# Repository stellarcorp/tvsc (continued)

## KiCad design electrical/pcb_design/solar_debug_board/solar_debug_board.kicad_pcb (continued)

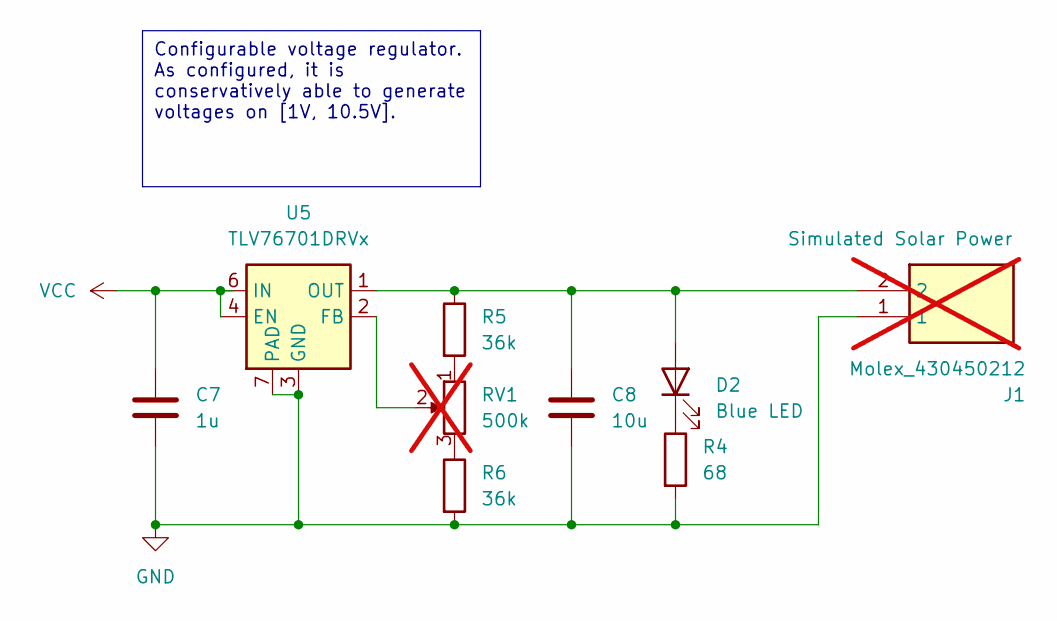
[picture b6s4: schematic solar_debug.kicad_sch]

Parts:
C7: 1u; C_0805_2012Metric; MPN C726584
C8: 10u; Nondescript_C_0603_1608Metric; MPN C344022
D2: Blue LED; LED_0603_1608Metric; MPN C72041
J1: Molex_430450212; Manufacturer Part Number 430450212; not fitted
R4: 68; R_0402_1005Metric; MPN C163455
R5, R6: 36k; R_0402_1005Metric; MPN C852742
RV1: 500k; Potentiometer_Bourns_3339H_Vertical; Tolerance 20%; Manufacturer Part Number 3339H-1-504LF; not fitted
U5: TLV76701DRVx; WSON-6-1EP_2x2mm_P0.65mm_EP1x1.6mm_ThermalVias; MPN C2863998

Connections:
GND: C7.2, C8.2, J1.1, R4.2, R6.2, U5.3 (GND), U5.5 (GND), U5.7 (PAD); also elsewhere on the board
unnamed: C8.1, D2.2 (A), J1.2, R5.1, U5.1 (OUT)
unnamed: D2.1 (K), R4.1
unnamed: R5.2, RV1.1
unnamed: R6.1, RV1.3
unnamed: RV1.2, U5.2 (FB)
VCC: C7.1, U5.4 (EN), U5.6 (IN); also elsewhere on the board

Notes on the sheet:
Configurable voltage regulator. As configured, it is conservatively able to generate voltages on [1V, 10.5V].

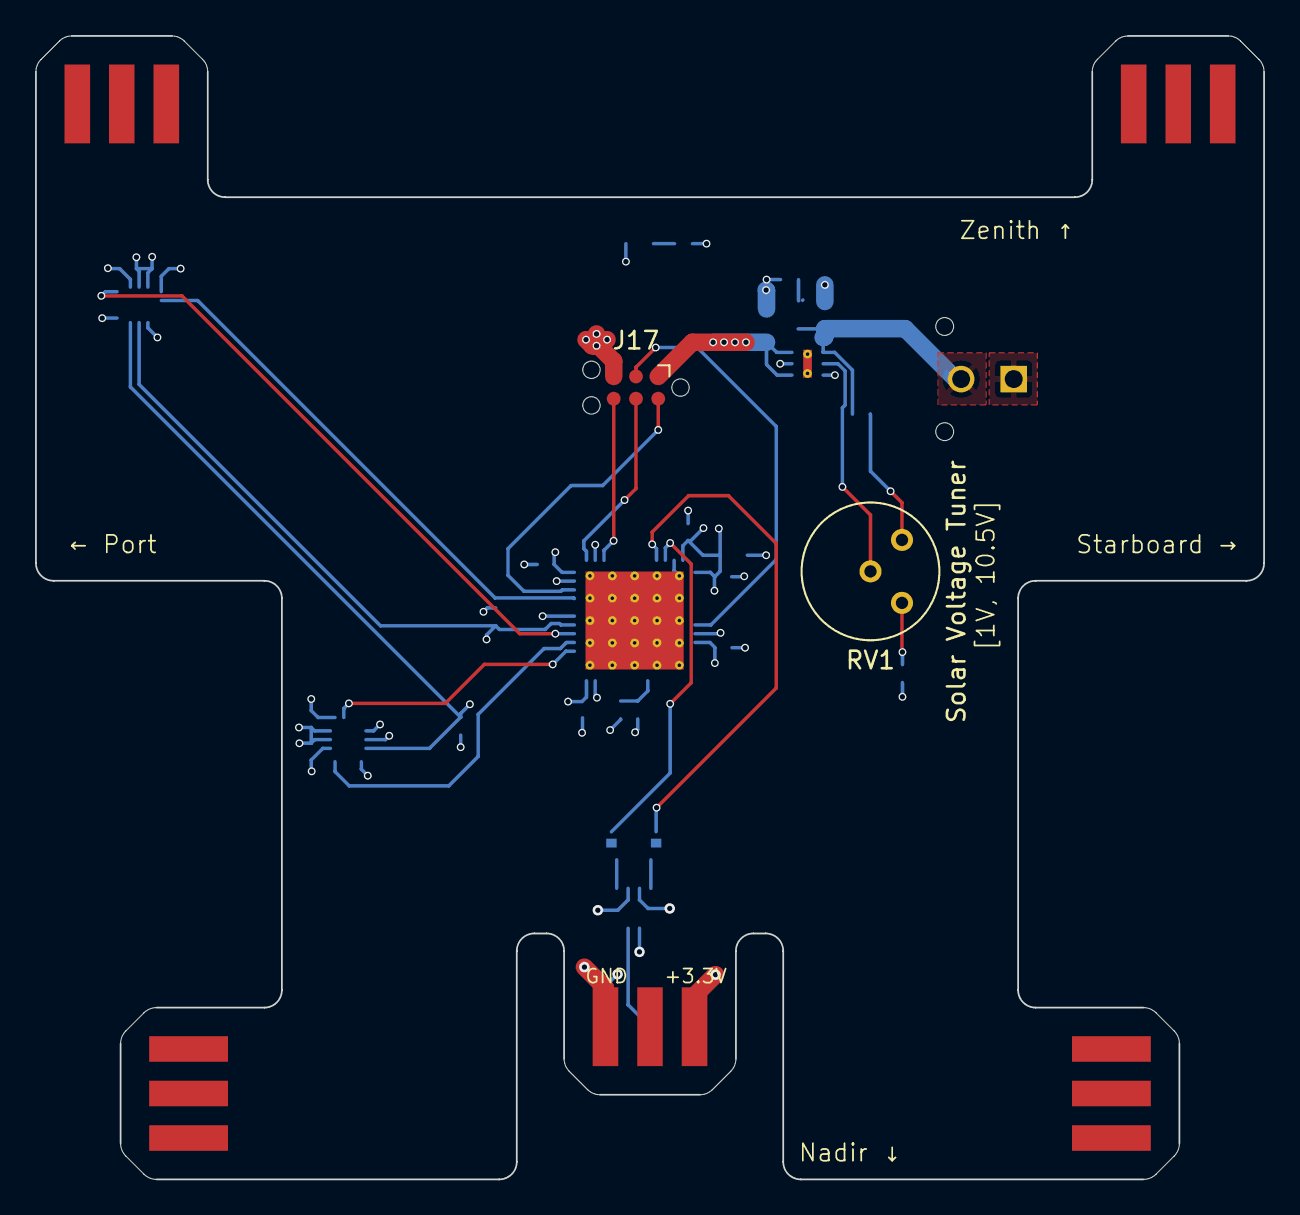
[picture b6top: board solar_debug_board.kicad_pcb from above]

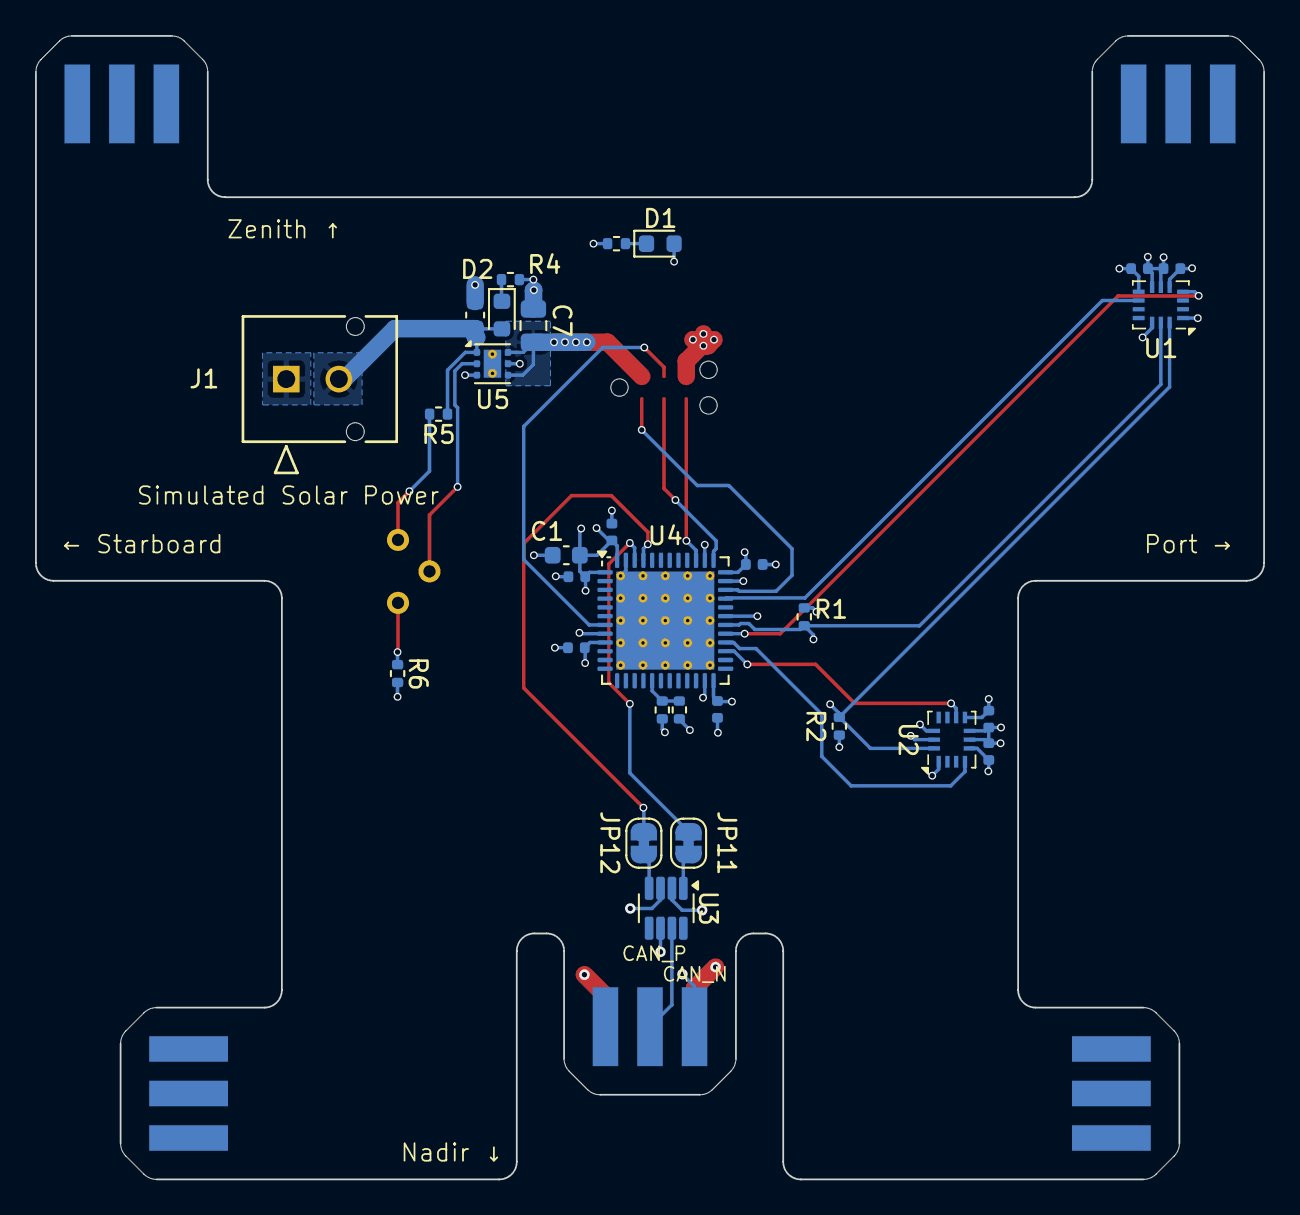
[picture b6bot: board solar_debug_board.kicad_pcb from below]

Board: 4 copper layers, 70.1 x 65.2 mm, 33 parts (30 on the bottom side), 27 nets.

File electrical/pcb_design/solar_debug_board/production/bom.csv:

Designator,Footprint,Quantity,Value,LCSC Part #
C1,0603,1,10u,C344022
"C10, C11, C12, C2, C3, C4, C5, C6, C9",Nondescript_C_0402_1005Metric,9,100n,C2649549
C7,0805,1,1u,C726584
C8,Nondescript_C_0603_1608Metric,1,10u,C344022
"D1, D2",0603,2,Blue LED,C72041
"JP11, JP12",SolderJumper-2_P1.3mm_Bridged_RoundedPad1.0x1.5mm,2,SolderJumper_2_Bridged,
"R1, R2",0402,2,1k5,C25867
R3,Nondescript_R_0402_1005Metric,1,2.21k,C305298
R4,0402,1,68,C163455
"R5, R6",0402,2,36k,C852742
R7,Nondescript_R_0402_1005Metric,1,301k,C25775
R8,Nondescript_R_0402_1005Metric,1,715k,C270585
"U1, U2",Bosch_LGA-14_3x2.5mm_P0.5mm,2,BMI323,C5368700
U3,SOT-23-8,1,TCAN330,C2877587
U4,QFN-48-1EP_7x7mm_P0.5mm_EP5.6x5.6mm_ThermalVias,1,STM32L452CEU6,C222355
U5,WSON-6-1EP_2x2mm_P0.65mm_EP1x1.6mm_ThermalVias,1,TLV76701DRVx,C2863998

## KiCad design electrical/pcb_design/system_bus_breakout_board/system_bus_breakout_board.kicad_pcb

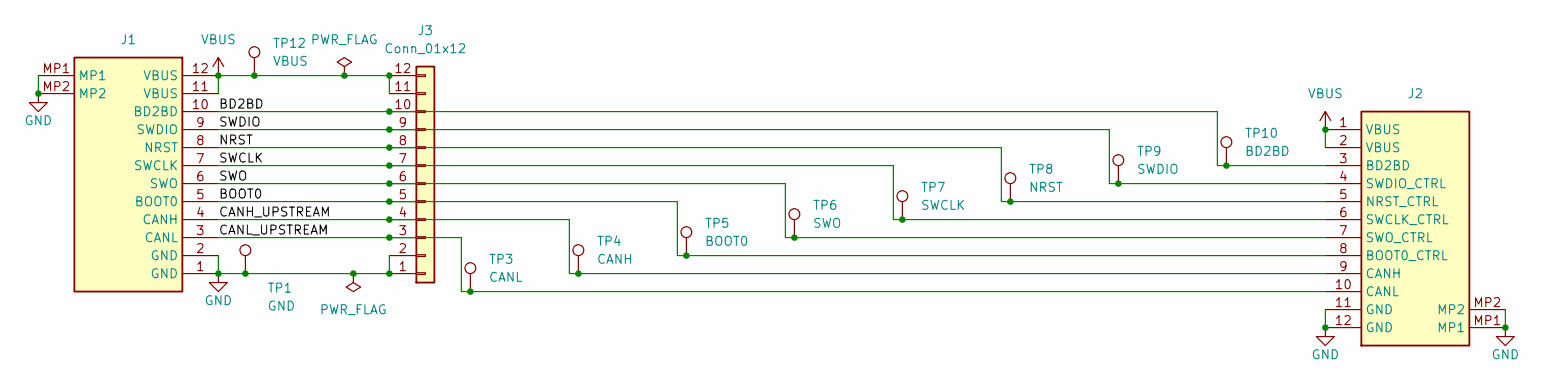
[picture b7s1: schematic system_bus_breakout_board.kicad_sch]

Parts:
J1: Molex_504050-1291; Bus Connector (Target); Manufacturer Part Number 504050-1291
J2: Molex_504050-1291; Bus Connector (Control); Manufacturer Part Number 504050-1291
J3: Conn_01x12; PinHeader_1x12_P2.54mm_Vertical
TP1: GND; Keystone_5000; Manufacturer Part Number 5000
TP3: CANL; Keystone_5000; Manufacturer Part Number 5000
TP4: CANH; Keystone_5000; Manufacturer Part Number 5000
TP5: BOOT0; Keystone_5000; Manufacturer Part Number 5000
TP6: SWO; Keystone_5000; Manufacturer Part Number 5000
TP7: SWCLK; Keystone_5000; Manufacturer Part Number 5000
TP8: NRST; Keystone_5000; Manufacturer Part Number 5000
TP9: SWDIO; Keystone_5000; Manufacturer Part Number 5000
TP10: BD2BD; Keystone_5000; Manufacturer Part Number 5000
TP12: VBUS; Keystone_5000; Manufacturer Part Number 5000

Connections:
/BD2BD: J1.10 (BD2BD), J2.3 (BD2BD), J3.10, TP10.1
/BOOT0: J1.5 (BOOT0), J2.8 (BOOT0_CTRL), J3.5, TP5.1
/CANH_UPSTREAM: J1.4 (CANH), J2.9 (CANH), J3.4, TP4.1
/CANL_UPSTREAM: J1.3 (CANL), J2.10 (CANL), J3.3, TP3.1
/NRST: J1.8 (NRST), J2.5 (NRST_CTRL), J3.8, TP8.1
/SWCLK: J1.7 (SWCLK), J2.6 (SWCLK_CTRL), J3.7, TP7.1
/SWDIO: J1.9 (SWDIO), J2.4 (SWDIO_CTRL), J3.9, TP9.1
/SWO: J1.6 (SWO), J2.7 (SWO_CTRL), J3.6, TP6.1
GND: J1.1 (GND), J1.2 (GND), J1.MP1, J1.MP2, J2.11 (GND), J2.12 (GND), J2.MP1, J2.MP2, J3.1, J3.2, TP1.1
VBUS: J1.11 (VBUS), J1.12 (VBUS), J2.1 (VBUS), J2.2 (VBUS), J3.11, J3.12, TP12.1

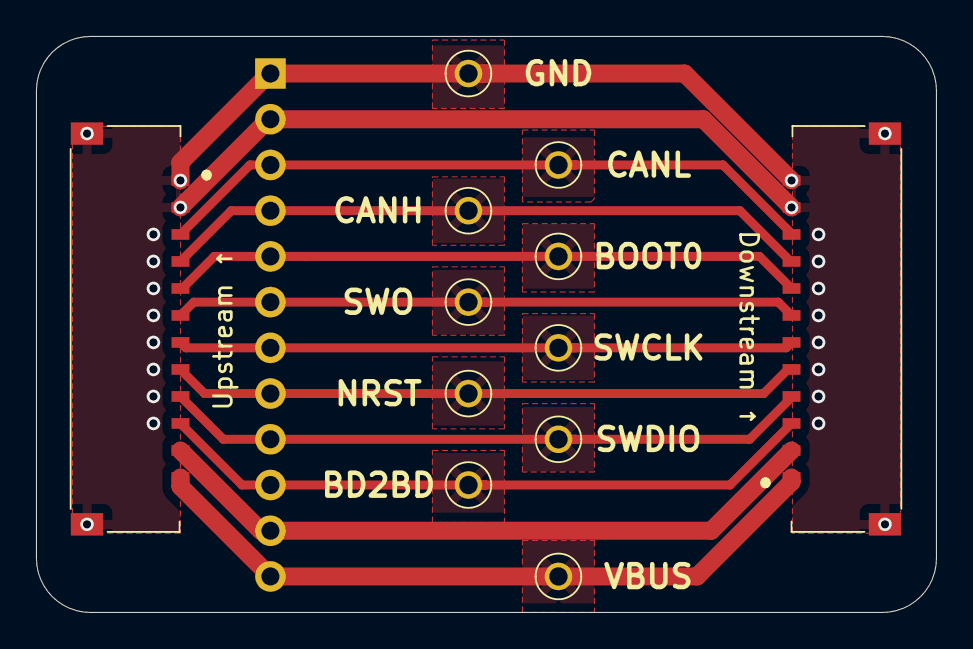
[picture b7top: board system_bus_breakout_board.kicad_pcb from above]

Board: 2 copper layers, 50.0 x 32.0 mm, 13 parts (1 on the bottom side), 10 nets.

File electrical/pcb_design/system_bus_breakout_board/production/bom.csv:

Designator,Footprint,Quantity,Value,LCSC Part #
J1,Bus Connector (Target),1,Molex_504050-1291,C563982
J2,Bus Connector (Control),1,Molex_504050-1291,C563982
J3,PinHeader_1x12_P2.54mm_Vertical,1,Conn_01x12,
TP1,Keystone_5000,1,GND,C5199900
TP10,Keystone_5000,1,BD2BD,C5199900
TP12,Keystone_5000,1,VBUS,C5199900
TP3,Keystone_5000,1,CANL,C5199900
TP4,Keystone_5000,1,CANH,C5199900
TP5,Keystone_5000,1,BOOT0,C5199900
TP6,Keystone_5000,1,SWO,C5199900
TP7,Keystone_5000,1,SWCLK,C5199900
TP8,Keystone_5000,1,NRST,C5199900
TP9,Keystone_5000,1,SWDIO,C5199900

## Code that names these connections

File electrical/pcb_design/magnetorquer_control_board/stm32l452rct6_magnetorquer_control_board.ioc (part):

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Mcu.Name=STM32L452R(C-E)Tx
Mcu.Package=LQFP64
Mcu.UserName=STM32L452RCTx
PA10.GPIOParameters=GPIO_Label
PA10.GPIO_Label=CAN1_SILENT
PA10.Signal=GPIO_Output
PA11.Mode=CAN_Activate
PA11.Signal=CAN1_RX
PA12.Mode=CAN_Activate
PA12.Signal=CAN1_TX
PA13\ (JTMS/SWDIO).Mode=Serial_Wire
PA13\ (JTMS/SWDIO).Signal=SYS_JTMS-SWDIO
PA14\ (JTCK/SWCLK).Mode=Serial_Wire
PA14\ (JTCK/SWCLK).Signal=SYS_JTCK-SWCLK
PA6.GPIOParameters=GPIO_Label
PA6.GPIO_Label=BOARD_ID_POWER
PA6.Signal=GPIO_Output
PA7.GPIOParameters=GPIO_Label
PA7.GPIO_Label=BOARD_ID_SENSE
PA7.Signal=ADCx_IN12
PA9.GPIOParameters=GPIO_Label
PA9.GPIO_Label=CAN1_SHUTDOWN
PA9.Signal=GPIO_Output
PB10.Mode=I2C
PB10.Signal=I2C2_SCL
PB11.Mode=I2C
PB11.Signal=I2C2_SDA
PB12.GPIOParameters=GPIO_Label
PB12.GPIO_Label=SWO_CONTROL
PB12.Signal=GPIO_Output
PB13.GPIOParameters=GPIO_Label
PB13.GPIO_Label=SWCLK_CONTROL
PB13.Signal=GPIO_Output
PB14.GPIOParameters=GPIO_Label
PB14.GPIO_Label=NRST_CONTROL
PB14.Signal=GPIO_Output
PB15.GPIOParameters=GPIO_Label
PB15.GPIO_Label=SWDIO_CONTROL
PB15.Signal=GPIO_Output
PB3\ (JTDO/TRACESWO).Signal=SYS_JTDO-SWO
PB6.Mode=I2C
PB6.Signal=I2C1_SCL
PB7.Mode=I2C
PB7.Signal=I2C1_SDA
PB8.GPIOParameters=GPIO_PuPd,GPIO_Label
PB8.GPIO_Label=NMAG_FAULT
PB8.GPIO_PuPd=GPIO_PULLUP
PB8.Signal=GPIO_Input
PB9.GPIOParameters=GPIO_Label
PB9.GPIO_Label=BOOT0_CONTROL
PB9.Signal=GPIO_Output
PC0.Mode=I2C
PC0.Signal=I2C3_SCL
PC1.Mode=I2C
PC1.Signal=I2C3_SDA
PC10.Mode=Full_Duplex_Master
PC10.Signal=SPI3_SCK
PC11.Mode=Full_Duplex_Master
PC11.Signal=SPI3_MISO
PC12.Mode=Full_Duplex_Master
PC12.Signal=SPI3_MOSI
PC13.GPIOParameters=GPIO_Label
PC13.GPIO_Label=DEBUG_LED
PC13.Signal=GPIO_Output
PC14-OSC32_IN\ (PC14).GPIOParameters=GPIO_Label
PC14-OSC32_IN\ (PC14).GPIO_Label=IMU1_SPI_CS
PC14-OSC32_IN\ (PC14).Signal=GPIO_Output
PC15-OSC32_OUT\ (PC15).GPIOParameters=GPIO_Label
PC15-OSC32_OUT\ (PC15).GPIO_Label=IMU_MAG_INT1
PC15-OSC32_OUT\ (PC15).Signal=GPIO_Input
PC2.GPIOParameters=GPIO_Label
PC2.GPIO_Label=IMU1_INT1
PC2.Signal=GPXTI2
PC3.GPIOParameters=GPIO_Label
PC3.GPIO_Label=IMU1_INT2
PC3.Signal=GPXTI3
PC6.GPIOParameters=GPIO_Label
PC6.GPIO_Label=IMU2_INT2
PC6.Signal=GPXTI6
PC7.GPIOParameters=GPIO_Label
PC7.GPIO_Label=IMU2_INT1
PC7.Signal=GPXTI7
PC8.GPIOParameters=GPIO_Label
PC8.GPIO_Label=IMU_MAG_SPI_CS
PC8.Signal=GPIO_Output
PC9.GPIOParameters=GPIO_Label
PC9.GPIO_Label=IMU2_SPI_CS
PC9.Signal=GPIO_Output
RCC.HSE_VALUE=8000000
RCC.SYSCLKFreq_VALUE=16000000
RCC.SYSCLKSource=RCC_SYSCLKSOURCE_PLLCLK
board=custom
